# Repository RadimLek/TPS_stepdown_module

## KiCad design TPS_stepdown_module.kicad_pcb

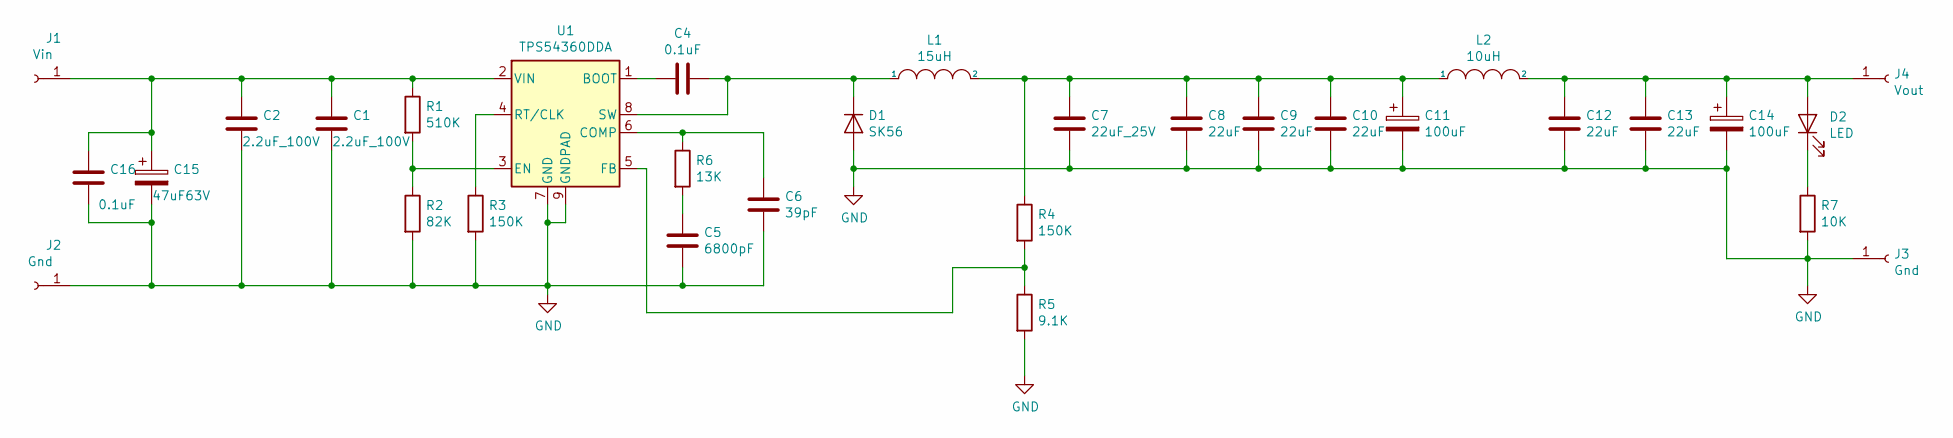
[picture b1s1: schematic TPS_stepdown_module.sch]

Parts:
C1, C2: 2.2uF_100V; C_1812_4532Metric_Pad1.30x3.40mm_HandSolder
C4, C16: 0.1uF; C_1206_3216Metric
C5: 6800pF; C_1206_3216Metric
C6: 39pF; C_0805_2012Metric_Pad1.15x1.40mm_HandSolder
C7: 22uF_25V; C_1210_3225Metric
C8, C9, C10, C12, C13: 22uF; C_1210_3225Metric
C11, C14: 100uF; CP_Radial_D6.3mm_P2.50mm
C15: 47uF63V; CP_Radial_D6.3mm_P2.50mm
D1: SK56; D_SMB
D2: LED; LED_1206_3216Metric_Castellated
J1: Vin; PinSocket_1x01_P2.54mm_Vertical
J2, J3: Gnd; PinSocket_1x01_P2.54mm_Vertical
J4: Vout; PinSocket_1x01_P2.54mm_Vertical
L1: 15uH; EPCOS_B82477G4
L2: 10uH; EPCOS_B82477G4
R1: 510K; R_1206_3216Metric
R2: 82K; R_1206_3216Metric
R3, R4: 150K; R_1206_3216Metric
R5: 9.1K; R_1206_3216Metric
R6: 13K; R_1206_3216Metric
R7: 10K; R_1206_3216Metric_Pad1.42x1.75mm_HandSolder
U1: TPS54360DDA; TI_SO-PowerPAD-8_ThermalVias

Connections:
GND: C1.2, C2.2, C5.1, C6.1, C7.2, C8.2, C9.2, C10.2, C11.2, C12.2, C13.2, C14.2, C15.2, C16.2, D1.2 (A), J2.1, J3.1, R2.2, R3.2, R5.2, R7.2, U1.7 (GND), U1.9 (GNDPAD)
unnamed: C1.1, C2.1, C15.1, C16.1, J1.1, R1.1, U1.2 (VIN)
unnamed: C4.1, D1.1 (K), L1.1, U1.8 (SW)
unnamed: C4.2, U1.1 (BOOT)
unnamed: C5.2, R6.2
unnamed: C6.2, R6.1, U1.6 (COMP)
unnamed: C7.1, C8.1, C9.1, C10.1, C11.1, L1.2, L2.1, R4.1
unnamed: C12.1, C13.1, C14.1, D2.2 (A), J4.1, L2.2
unnamed: D2.1 (K), R7.1
unnamed: R1.2, R2.1, U1.3 (EN)
unnamed: R3.1, U1.4 (RT/CLK)
unnamed: R4.2, R5.1, U1.5 (FB)

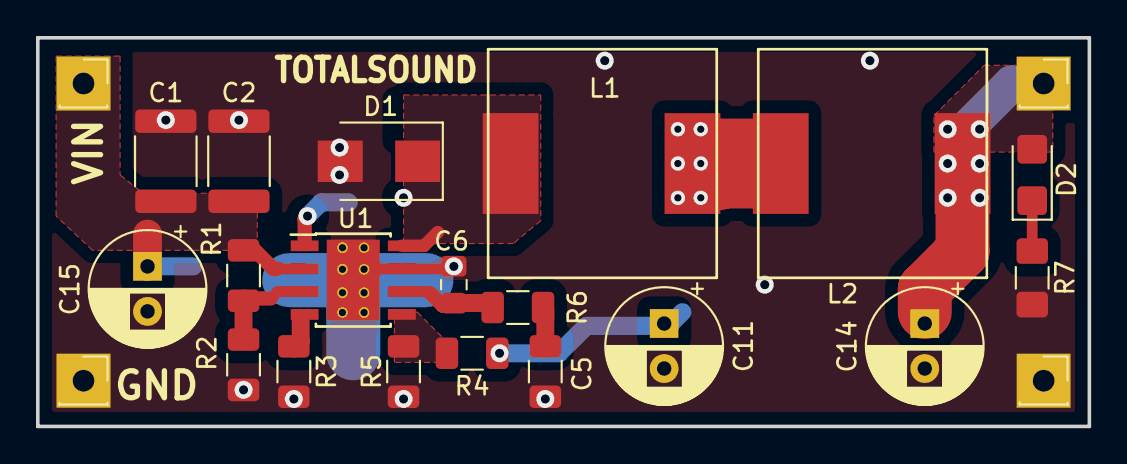
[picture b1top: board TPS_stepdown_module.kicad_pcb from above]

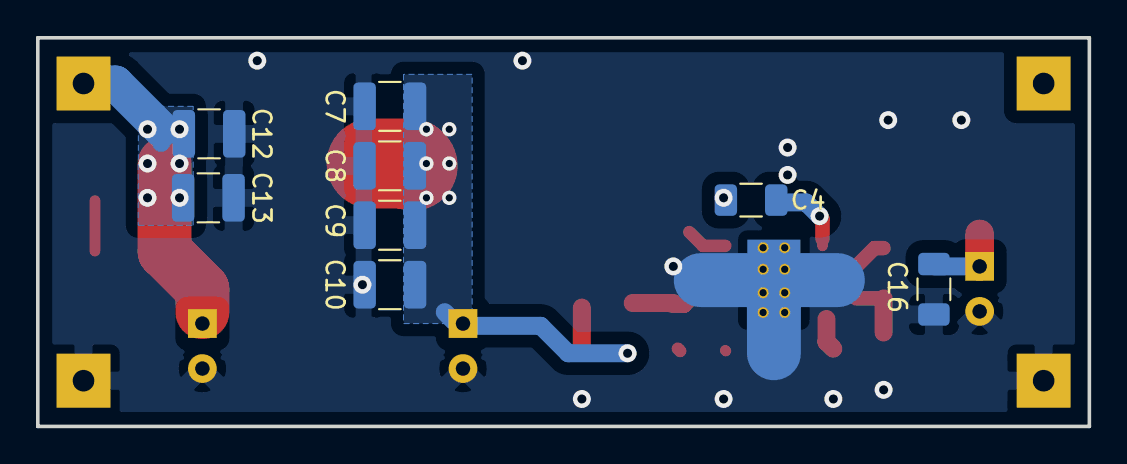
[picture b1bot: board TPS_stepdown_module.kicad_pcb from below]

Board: 2 copper layers, 58.4 x 21.6 mm, 31 parts (8 on the bottom side), 12 nets.

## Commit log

2020-07-03 заменил 0805 на 1206
2020-08-07 изменил размеры входной керамики
